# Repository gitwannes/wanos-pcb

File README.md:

# wanos-pcb

KiCad design and JLCPCB fabrication for **wanos-pcb-v1** — first-generation WanOS Pi carrier.

**Today:** WanOS runs on **WISC** boards (legacy reference in-repo). **Target:** **wanos-pcb-v1** + updated **wanos**. Code → [gitwannes/wanos](https://github.com/gitwannes/wanos).

---

## Repository layout

```text
wanos-pcb/
├── docs/
│   ├── board-spec.md            # wanos-pcb-v1 electrical spec (canonical)
│   ├── remotepcb.md             # wanos-remote plant module
│   ├── field-wiring.md          # JST pinouts + Cat5
│   ├── gpio-interface.md        # Pi BCM map (R2)
│   ├── external-plant.md        # Off-board SSR + 12 V
│   ├── grounding.md
│   ├── reference/
│   │   ├── datasheets/          # PDF pack (gitignored binaries)
│   │   ├── silkscreen/
│   │   └── wisc-board/
│   └── todo/
├── projects/wanos-board/        # Main Pi carrier
│   ├── wanos-board.kicad_pro
│   ├── components.xlsx          # BOM: column board = main | remote
│   └── …
├── projects/wanos-remote/       # Plant remote (pulse + 1-Wire)
│   ├── wanos-remote.kicad_pro
│   ├── wanos-remote.kicad_sch
│   └── design.yaml
└── README.md
```

---

## Pipeline (summary)

| Step | Id | What |
|---|---|---|
| ~~…~~ | ~~**R / Ops1 / S / Gate-S1**~~ | ~~Requirements + main schematic~~ **Done** **2026-09-21** |
| **1** | **Ops-Remote1** | Operator: clean + check **wanos-remote** schematic |
| **2** | **L1** | Main carrier PCB layout |
| **3** | **Gate-L1** | Layout sign-off |
| **4–5** | **Ops2, J1** | Fab readiness + JLCPCB order |
| **6** | **Ops3** | Receiving inspection |
| **7–8** | **V1a, V1b** | Bring-up / extended software |

Full backlog → [`docs/todo/pipeline.md`](docs/todo/pipeline.md).

---

## Quick links

| Doc | Purpose |
|---|---|
| [`docs/board-spec.md`](docs/board-spec.md) | **wanos-pcb-v1** specification |
| [`docs/remotepcb.md`](docs/remotepcb.md) | **wanos-remote** plant module |
| [`docs/gpio-interface.md`](docs/gpio-interface.md) | Pi BCM + software strategy (**wanos-pcb-v1**) |
| [`docs/gpio-map.md`](docs/gpio-map.md) | WISC production BCM inventory |
| [`docs/external-plant.md`](docs/external-plant.md) | DIN SSR + 12 V plant |
| [`docs/field-wiring.md`](docs/field-wiring.md) | Connector pinouts |
| [`docs/schematic-signoff.md`](docs/schematic-signoff.md) | Gate-S1 record (Done) |
| [`docs/reference/datasheets/README.md`](docs/reference/datasheets/README.md) | Datasheet pack |
| [`docs/kicad-setup.md`](docs/kicad-setup.md) | Konnect + KiCad 10 (**Ops1** Done) |
| [`projects/wanos-board/components.xlsx`](projects/wanos-board/components.xlsx) | BOM / LCSC seed |

---

## Workflow

1. ~~**`kickoff` / S1 / Gate-S1**~~ — **Done** (schematic signed **2026-09-21**).
2. **Ops-Remote1** — operator cleans + checks [`projects/wanos-remote/`](projects/wanos-remote/).
3. **`implement` L1** — main carrier layout (after Gate-S1).
4. **`V1a`** — board + updated **wanos**; cutover from WISC.

**DoD (every phase):** audit all `docs/**/*.md` + this README.

---

## Related repos

| Repo | Role |
|---|---|
| [gitwannes/wanos](https://github.com/gitwannes/wanos) | Runtime (WISC today; wanos-pcb-v1 at **V1a**) |
| [Konnect](https://github.com/mixelpixx/Konnect) | KiCad MCP automation |

---

## License

Source available — personal use OK, no redistribution. See [LICENSE](LICENSE).

Copyright (c) 2026 [Johan Wannes Hofmans](https://github.com/gitwannes). All rights reserved.

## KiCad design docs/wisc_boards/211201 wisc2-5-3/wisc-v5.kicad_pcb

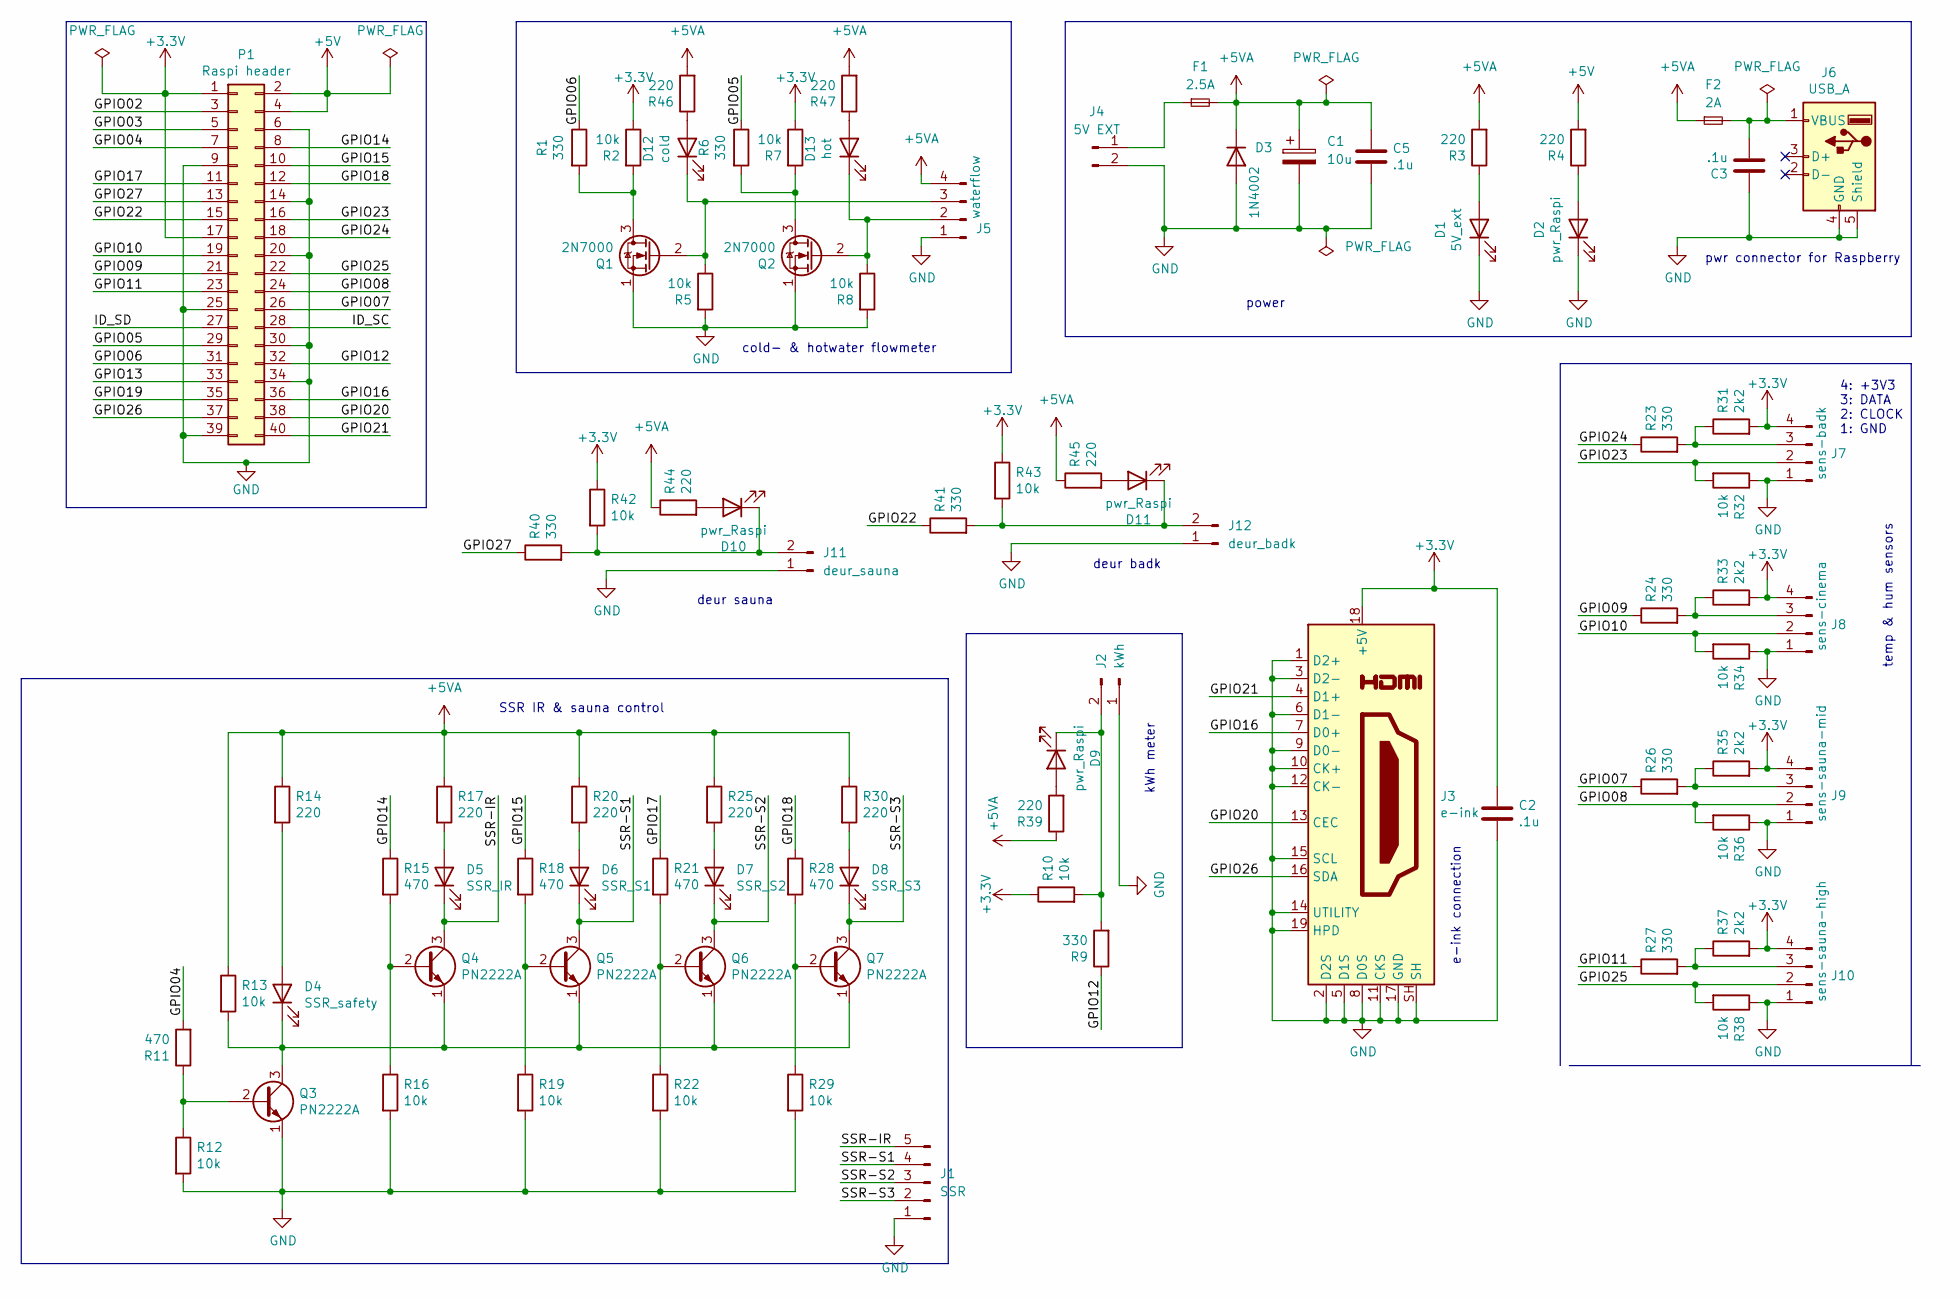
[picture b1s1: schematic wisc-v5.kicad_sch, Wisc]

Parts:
C1: 10u; CP_Radial_D5.0mm_P2.50mm
C2, C3, C5: .1u; C_Disc_D5.0mm_W2.5mm_P5.00mm
D1: 5V_ext; LED_D3.0mm
D2, D9, D10, D11: pwr_Raspi; LED_D3.0mm
D3: 1N4002; D_DO-41_SOD81_P10.16mm_Horizontal
D4: SSR_safety; LED_D3.0mm
D5: SSR_IR; LED_D3.0mm
D6: SSR_S1; LED_D3.0mm
D7: SSR_S2; LED_D3.0mm
D8: SSR_S3; LED_D3.0mm
D12: cold; LED_D3.0mm
D13: hot; LED_D3.0mm
F1: 2.5A; Fuseholder_Cylinder-5x20mm_Schurter_0031_8201_Horizontal_Op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
F2: 2A; Fuseholder_Cylinder-5x20mm_Schurter_0031_8201_Horizontal_Op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
J1: SSR; JST_XH_B5B-XH-A_1x05_P2.50mm_Vertical
J2: kWh; JST_XH_B2B-XH-A_1x02_P2.50mm_Vertical
J3: e-ink; 17466791
J4: 5V EXT; JST_XH_B2B-XH-A_1x02_P2.50mm_Vertical
J5: waterflow; JST_XH_B4B-XH-A_1x04_P2.50mm_Vertical
J6: USB_A; USB_A_Molex_67643_Horizontal
J7: sens-badk; JST_XH_B4B-XH-A_1x04_P2.50mm_Vertical
J8: sens-cinema; JST_XH_B4B-XH-A_1x04_P2.50mm_Vertical
J9: sens-sauna-mid; JST_XH_B4B-XH-A_1x04_P2.50mm_Vertical
J10: sens-sauna-high; JST_XH_B4B-XH-A_1x04_P2.50mm_Vertical
J11: deur_sauna; JST_XH_B2B-XH-A_1x02_P2.50mm_Vertical
J12: deur_badk; JST_XH_B2B-XH-A_1x02_P2.50mm_Vertical
P1: Raspi header; PinHeader_2x20_P2.54mm_Vertical
Q1, Q2: 2N7000; TO-92_Inline
Q3, Q4, Q5, Q6, Q7: PN2222A; TO-92_Inline
R1, R6, R9, R23, R24, R26, R27, R40, R41: 330; R_Axial_DIN0207_L6.3mm_D2.5mm_P10.16mm_Horizontal
R2, R5, R7, R8, R10, R12, R13, R16, R19, R22, R29, R32, R34, R36, R38, R42, R43: 10k; R_Axial_DIN0207_L6.3mm_D2.5mm_P10.16mm_Horizontal
R3, R4, R14, R17, R20, R25, R30, R39, R44, R45, R46, R47: 220; R_Axial_DIN0207_L6.3mm_D2.5mm_P10.16mm_Horizontal
R11, R15, R18, R21, R28: 470; R_Axial_DIN0207_L6.3mm_D2.5mm_P10.16mm_Horizontal
R31, R33, R35, R37: 2k2; R_Axial_DIN0207_L6.3mm_D2.5mm_P10.16mm_Horizontal

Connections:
+3V3: C2.1, J3.18 (+5V), J7.4, J8.4, J9.4, J10.4, P1.1, P1.17, R2.1, R7.1, R10.1, R31.2, R33.2, R35.2, R37.2, R42.1, R43.1
+5V: P1.2, P1.4, R4.2
+5VA: C1.1, C5.1, D3.1 (K), F1.2, F2.1, J5.4, R3.2, R13.1, R14.1, R17.1, R20.1, R25.1, R30.1, R39.1, R44.1, R45.1, R46.2, R47.2
/GPIO02: P1.3
/GPIO03: P1.5
/GPIO04: P1.7, R11.2
/GPIO05: P1.29, R6.1
/GPIO06: P1.31, R1.1
/GPIO07: P1.26, R26.1
/GPIO08: J9.2, P1.24, R36.2
/GPIO09: P1.21, R24.1
/GPIO10: J8.2, P1.19, R34.2
/GPIO11: P1.23, R27.1
/GPIO12: P1.32, R9.1
/GPIO13: P1.33
/GPIO14: P1.8, R15.1
/GPIO15: P1.10, R18.1
/GPIO16: J3.7 (D0+), P1.36
/GPIO17: P1.11, R21.1
/GPIO18: P1.12, R28.1
/GPIO19: P1.35
/GPIO20: J3.13 (CEC), P1.38
/GPIO21: J3.4 (D1+), P1.40
/GPIO22: P1.15, R41.1
/GPIO23: J7.2, P1.16, R32.2
/GPIO24: P1.18, R23.1
/GPIO25: J10.2, P1.22, R38.2
/GPIO26: J3.16 (SDA), P1.37
/GPIO27: P1.13, R40.1
/ID_SC: P1.28
/ID_SD: P1.27
/SSR-IR: D5.1 (K), J1.5, Q4.3 (C)
/SSR-S1: D6.1 (K), J1.4, Q5.3 (C)
/SSR-S2: D7.1 (K), J1.3, Q6.3 (C)
/SSR-S3: D8.1 (K), J1.2, Q7.3 (C)
GND: C1.2, C2.2, C3.1, C5.2, D1.1 (K), D2.1 (K), D3.2 (A), J1.1, J2.1, J3.1 (D2+), J3.2 (D2S), J3.3 (D2-), J3.5 (D1S), J3.6 (D1-), J3.8 (D0S), J3.9 (D0-), J3.10 (CK+), J3.11 (CKS), J3.12 (CK-), J3.14 (UTILITY), J3.15 (SCL), J3.17 (GND), J3.19 (HPD), J3.SH, J4.2, J5.1, J6.4 (GND), J6.5 (Shield), J7.1, J8.1, J9.1, J10.1, J11.1, J12.1, P1.6, P1.9, P1.14, P1.20, P1.25, P1.30, P1.34, P1.39, Q1.1 (S), Q2.1 (S), Q3.1 (E), R5.2, R8.2, R12.2, R16.2, R19.2, R22.2, R29.2, R32.1, R34.1, R36.1, R38.1
unnamed: C3.2, F2.2, J6.1 (VBUS)
unnamed: D1.2 (A), R3.1
unnamed: D2.2 (A), R4.1
unnamed: D4.1 (K), Q3.3 (C), Q4.1 (E), Q5.1 (E), Q6.1 (E), Q7.1 (E), R13.2
unnamed: D4.2 (A), R14.2
unnamed: D5.2 (A), R17.2
unnamed: D6.2 (A), R20.2
unnamed: D7.2 (A), R25.2
unnamed: D8.2 (A), R30.2
unnamed: D9.1 (K), J2.2, R9.2, R10.2
unnamed: D9.2 (A), R39.2
unnamed: D10.1 (K), J11.2, R40.2, R42.2
unnamed: D10.2 (A), R44.2
unnamed: D11.1 (K), J12.2, R41.2, R43.2
unnamed: D11.2 (A), R45.2
unnamed: D12.1 (K), J5.3, Q1.2 (G), R5.1
unnamed: D12.2 (A), R46.1
unnamed: D13.1 (K), J5.2, Q2.2 (G), R8.1
unnamed: D13.2 (A), R47.1
unnamed: F1.1, J4.1
unnamed: J7.3, R23.2, R31.1
unnamed: J8.3, R24.2, R33.1
unnamed: J9.3, R26.2, R35.1
unnamed: J10.3, R27.2, R37.1
unnamed: Q1.3 (D), R1.2, R2.2
unnamed: Q2.3 (D), R6.2, R7.2
unnamed: Q3.2 (B), R11.1, R12.1
unnamed: Q4.2 (B), R15.2, R16.1
unnamed: Q5.2 (B), R18.2, R19.1
unnamed: Q6.2 (B), R21.2, R22.1
unnamed: Q7.2 (B), R28.2, R29.1

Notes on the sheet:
power
e-ink connection
deur badk
pwr connector for Raspberry
deur sauna
kWh meter
SSR IR & sauna control
temp & hum sensors
4: +3V3 3: DATA 2: CLOCK 1: GND
cold- & hotwater flowmeter

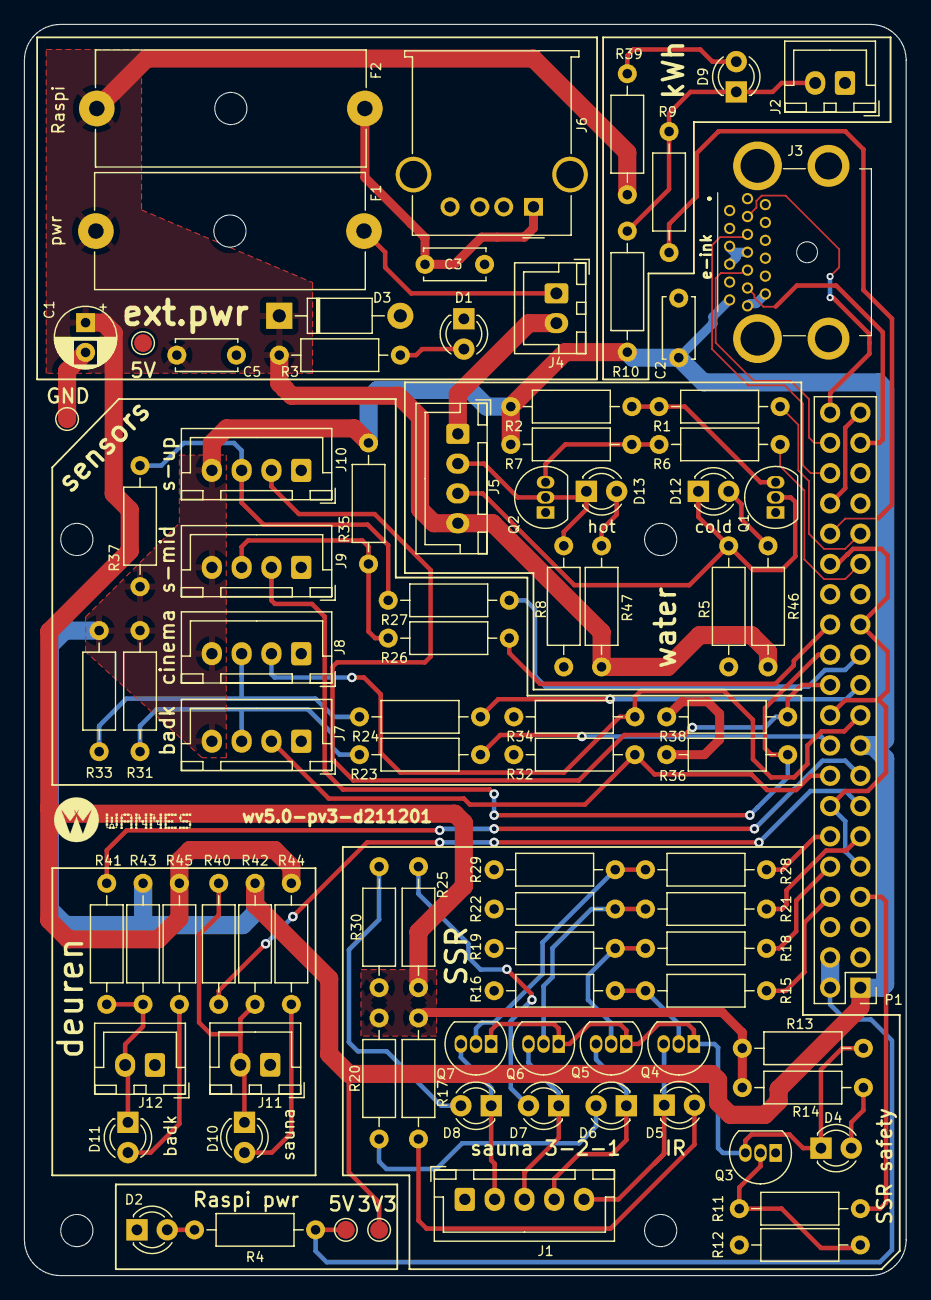
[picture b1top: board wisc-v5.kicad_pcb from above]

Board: 2 copper layers, 74.0 x 105.0 mm, 90 parts (0 on the bottom side), 61 nets.

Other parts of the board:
MK1, MK2, MK3, MK4: M2.5; MountingHole_2.7mm_M2.5

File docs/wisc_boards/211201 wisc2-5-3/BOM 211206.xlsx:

ref | value5 | # | type | value8 | needed | ordered
C1 | 10u | 1 | C | C/10u | 1 | 15
C2 | .1u | 2 | C | C/100n | 3 | 30
C3 | .1u | 3 | C
C5 | .1u | 5 | C
D1 | 5V_ext | 1 | D
D2 | pwr_Raspi | 2 | D
D3 | 1N4002 | 3 | D
D4 | SSR_safety | 4 | D
D5 | SSR_IR | 5 | D
D6 | SSR_S1 | 6 | D
D7 | SSR_S2 | 7 | D
D8 | SSR_S3 | 8 | D
D9 | pwr_Raspi | 9 | D
D10 | pwr_Raspi | 10 | D
D11 | pwr_Raspi | 11 | D
D12 | cold | 12 | D
D13 | hot | 13 | D
F1 | 2.5A | 1 | F
F2 | 2A | 2 | F
J2 | kWh | 2 | J | con2 | 4 | 40
J4 | 5V EXT | 4 | J | 2
J3 | e-ink | 3 | J | HDMI
J11 | deur_sauna | 11 | J | 2
J12 | deur_badk | 12 | J | 2
J6 | USB_A | 6 | J | USB
J5 | waterflow | 5 | J | con4 | 5 | 40
J7 | sens-badk | 7 | J | 4
J8 | sens-cinema | 8 | J | 4
J9 | sens-sauna-mid | 9 | J | 4
J10 | sens-sauna-high | 10 | J | 4
J1 | SSR | 1 | J | con5 | 1 | 10
P1 | Raspi header | 1 | P
Q1 | 2N7000 | 1 | Q | 2N7000 | 2 | 20
Q2 | 2N7000 | 2 | Q
Q3 | PN2222A | 3 | Q | PN2222A | 5 | replaced with 2N3904, 50 stuks
Q4 | PN2222A | 4 | Q
Q5 | PN2222A | 5 | Q
Q6 | PN2222A | 6 | Q
Q7 | PN2222A | 7 | Q
R2 | 10k | 2 | R | R/10k | 17 | 100
R5 | 10k | 5 | R
R7 | 10k | 7 | R
R8 | 10k | 8 | R
R10 | 10k | 10 | R
R12 | 10k | 12 | R
R13 | 10k | 13 | R
R16 | 10k | 16 | R
R19 | 10k | 19 | R
R22 | 10k | 22 | R
R29 | 10k | 29 | R
R32 | 10k | 32 | R
R34 | 10k | 34 | R
R36 | 10k | 36 | R
R38 | 10k | 38 | R
R42 | 10k | 42 | R
R43 | 10k | 43 | R
R3 | 220 | 3 | R | R/220 | 12 | 100
R4 | 220 | 4 | R
R14 | 220 | 14 | R
R17 | 220 | 17 | R
R20 | 220 | 20 | R
R25 | 220 | 25 | R
R30 | 220 | 30 | R
R39 | 220 | 39 | R
R44 | 220 | 44 | R
R45 | 220 | 45 | R
R46 | 220 | 46 | R
R47 | 220 | 47 | R
R31 | 2k2 | 31 | R | R/2k2 | 4 | 100
R33 | 2k2 | 33 | R
R35 | 2k2 | 35 | R
R37 | 2k2 | 37 | R
R1 | 330 | 1 | R | R/330 | 9 | 100
R6 | 330 | 6 | R
R9 | 330 | 9 | R
R23 | 330 | 23 | R
R24 | 330 | 24 | R
R26 | 330 | 26 | R
R27 | 330 | 27 | R
R40 | 330 | 40 | R
R41 | 330 | 41 | R
R11 | 470 | 11 | R | R/470 | 5 | 100
R15 | 470 | 15 | R
R18 | 470 | 18 | R
R21 | 470 | 21 | R
R28 | 470 | 28 | R
 |  | #VALUE!
 |  | #VALUE!
 |  | #VALUE!
 |  | #VALUE!
 |  | #VALUE!
 |  | #VALUE!
 |  | #VALUE!
 |  | #VALUE!
 |  | #VALUE!
 |  | #VALUE!
 |  | #VALUE!
 |  | #VALUE!
 |  | #VALUE!
 |  | #VALUE!
 |  | #VALUE!
 |  | #VALUE!
 |  | #VALUE!
 |  | #VALUE!
 |  | #VALUE!
 |  | #VALUE!
 |  | #VALUE!
 |  | #VALUE!
 |  | #VALUE!
 |  | #VALUE!
 |  | #VALUE!
 |  | #VALUE!
 |  | #VALUE!
 |  | #VALUE!
 |  | #VALUE!
 |  | #VALUE!
 |  | #VALUE!
 |  | #VALUE!
 |  | #VALUE!
 |  | #VALUE!
 |  | #VALUE!

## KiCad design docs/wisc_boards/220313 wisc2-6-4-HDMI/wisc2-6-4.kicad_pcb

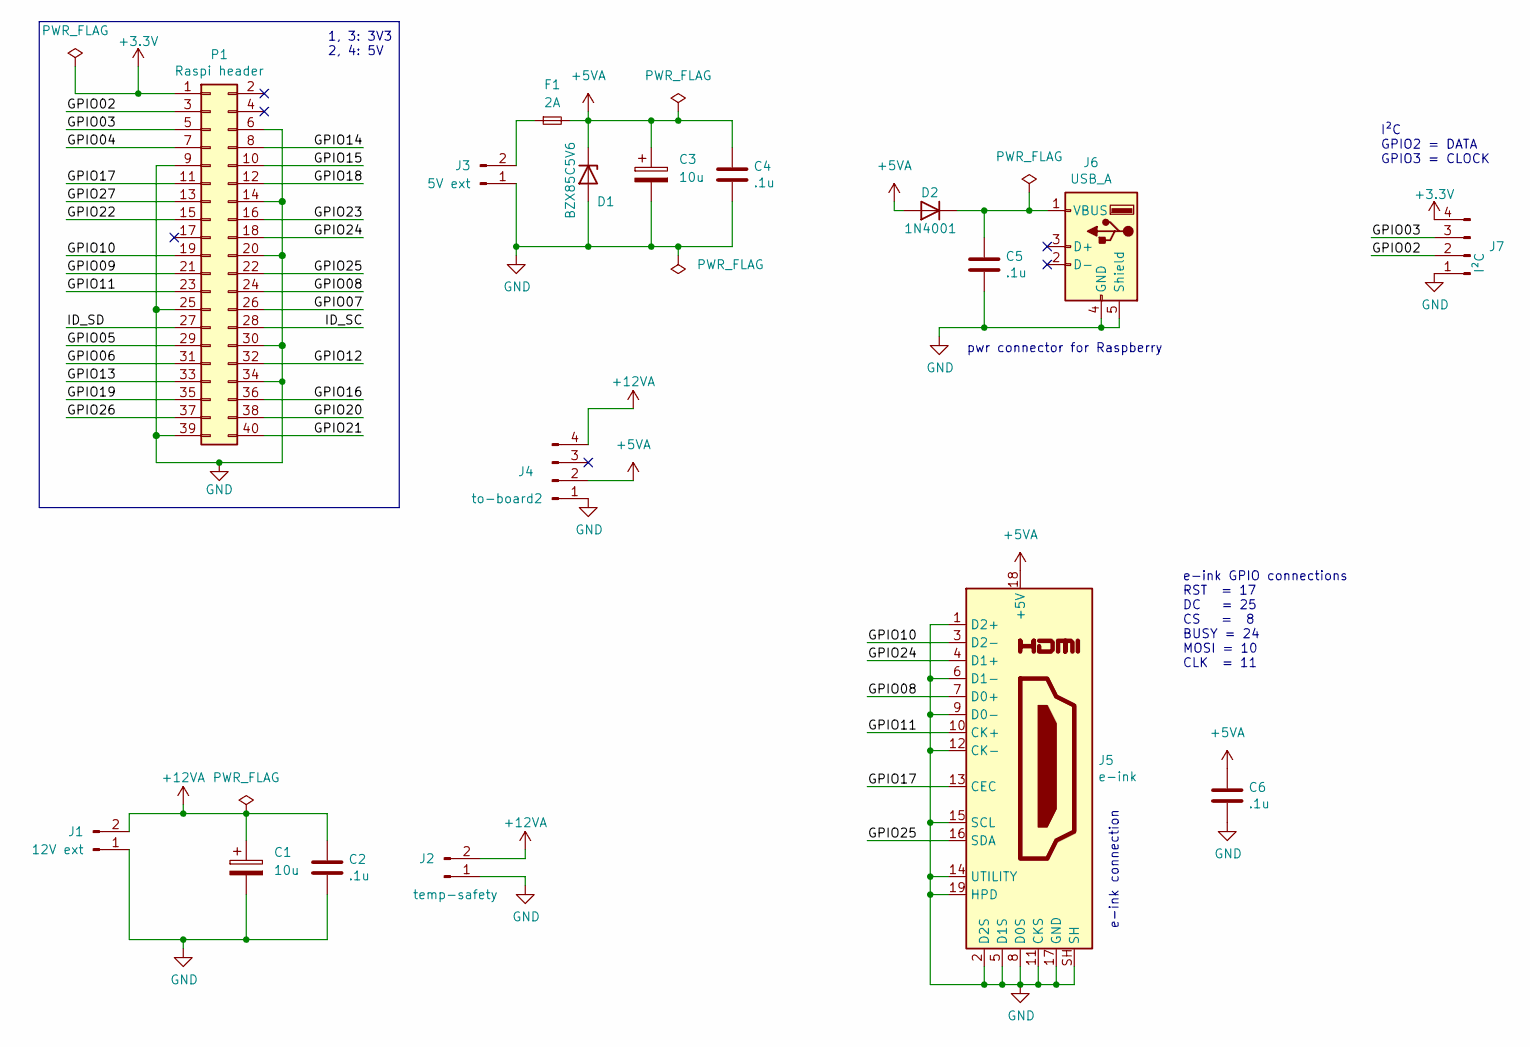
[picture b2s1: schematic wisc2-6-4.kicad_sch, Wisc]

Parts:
C1, C3: 10u; CP_Radial_D5.0mm_P2.50mm
C2, C4, C5, C6: .1u; C_Disc_D5.0mm_W2.5mm_P5.00mm
D1: BZX85C5V6; D_DO-41_SOD81_P7.62mm_Horizontal
D2: 1N4001; D_DO-41_SOD81_P7.62mm_Horizontal
F1: 2A; Fuseholder_Cylinder-5x20mm_Schurter_0031_8201_Horizontal_Op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
J1: 12V ext; JST_XH_B2B-XH-A_1x02_P2.50mm_Vertical
J2: temp-safety; JST_XH_B2B-XH-A_1x02_P2.50mm_Vertical
J3: 5V ext; JST_XH_B2B-XH-A_1x02_P2.50mm_Vertical
J4: to-board2; JST_XH_B4B-XH-A_1x04_P2.50mm_Vertical
J5: e-ink; 17466791
J6: USB_A; USB_A_Molex_67643_Horizontal
J7: I²C; JST_XH_B4B-XH-A_1x04_P2.50mm_Vertical
P1: Raspi header; PinHeader_2x20_P2.54mm_Vertical

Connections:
+3V3: J7.4, P1.1
+5VA: C3.1, C4.1, C6.1, D1.1 (K), D2.2 (A), F1.2, J4.2, J5.18 (+5V); also elsewhere on the board
+12VA: C1.1, C2.1, J1.2, J2.2, J4.4; also elsewhere on the board
/GPIO02: J7.2, P1.3
/GPIO03: J7.3, P1.5
/GPIO04: P1.7
/GPIO05: P1.29
/GPIO06: P1.31
/GPIO07: P1.26
/GPIO08: J5.7 (D0+), P1.24
/GPIO09: P1.21
/GPIO10: J5.3 (D2-), P1.19
/GPIO11: J5.10 (CK+), P1.23
/GPIO12: P1.32
/GPIO13: P1.33
/GPIO14: P1.8
/GPIO15: P1.10
/GPIO16: P1.36
/GPIO17: J5.13 (CEC), P1.11
/GPIO18: P1.12
/GPIO19: P1.35
/GPIO20: P1.38
/GPIO21: P1.40
/GPIO22: P1.15
/GPIO23: P1.16
/GPIO24: J5.4 (D1+), P1.18
/GPIO25: J5.16 (SDA), P1.22
/GPIO26: P1.37
/GPIO27: P1.13
/ID_SC: P1.28
/ID_SD: P1.27
GND: C1.2, C2.2, C3.2, C4.2, C5.2, C6.2, D1.2 (A), J1.1, J2.1, J3.1, J4.1, J5.1 (D2+), J5.2 (D2S), J5.5 (D1S), J5.6 (D1-), J5.8 (D0S), J5.9 (D0-), J5.11 (CKS), J5.12 (CK-), J5.14 (UTILITY), J5.15 (SCL), J5.17 (GND), J5.19 (HPD), J5.SH, J6.4 (GND), J6.5 (Shield), J7.1, P1.6, P1.9, P1.14, P1.20, P1.25, P1.30, P1.34, P1.39; also elsewhere on the board
unnamed: C5.1, D2.1 (K), J6.1 (VBUS)
unnamed: F1.1, J3.2

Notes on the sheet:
pwr connector for Raspberry
e-ink GPIO connections RST = 17 DC = 25 CS = 8 BUSY = 24 MOSI = 10 CLK = 11
I²C GPIO2 = DATA GPIO3 = CLOCK
e-ink connection
1, 3: 3V3 2, 4: 5V

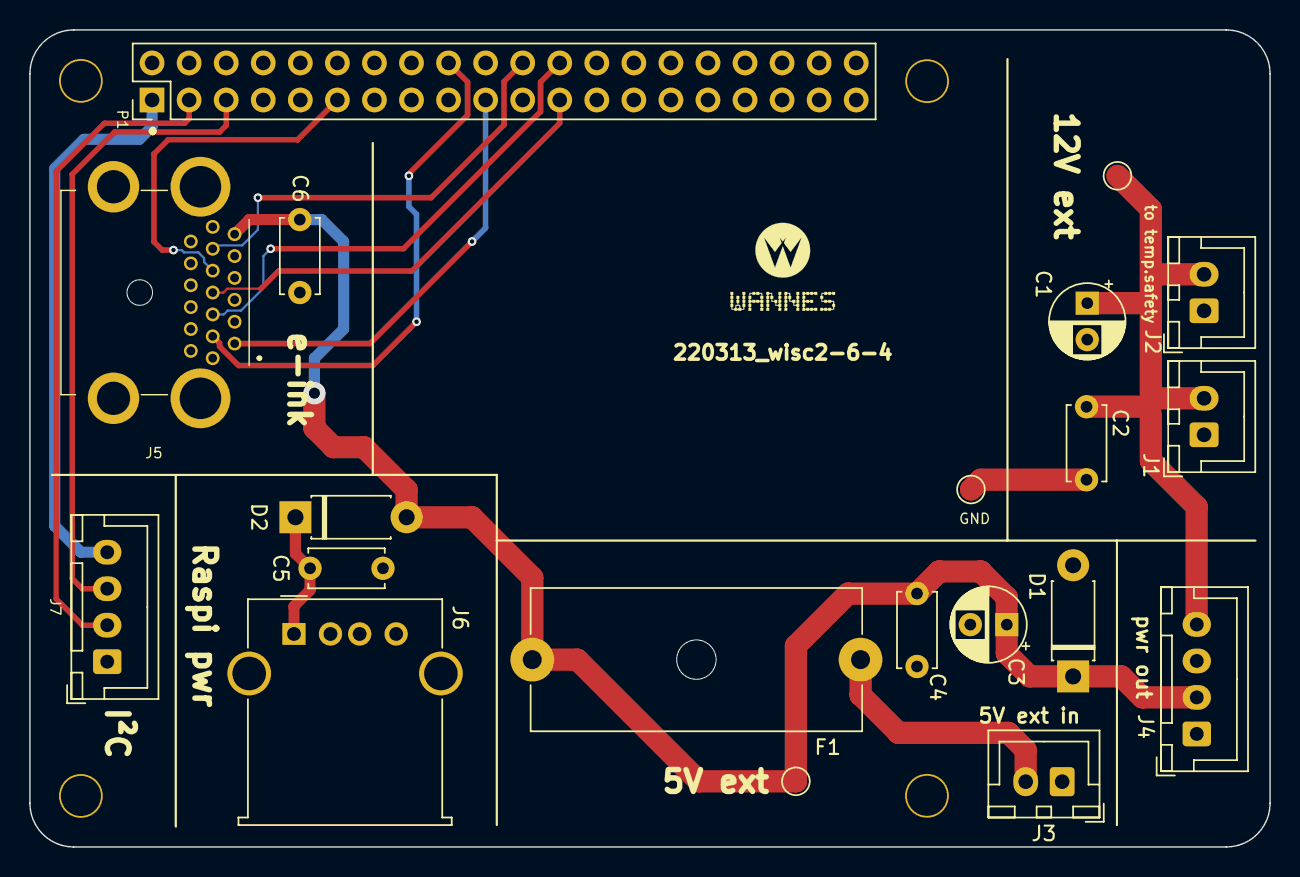
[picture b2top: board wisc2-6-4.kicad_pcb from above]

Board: 2 copper layers, 85.0 x 56.0 mm, 24 parts (0 on the bottom side), 14 nets.

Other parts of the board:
5VA, 12V: TestPoint_Pad_D1.5mm
GND: TestPoint_Pad_D1.5mm
H1, H2, H3, H4: 3mm_Mounting_Hole; NPTH_3mm_ID

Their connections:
+5VA: 5VA.1; also elsewhere on the board
+12VA: 12V.1; also elsewhere on the board
GND: GND.1; also elsewhere on the board
